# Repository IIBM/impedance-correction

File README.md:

# impedance-correction

This project involves the design, development and prototyping of an automated
**electrode impedance meter and corrector** for biological applications.

This will be achieved in the context of a basic embedded systems subject of the
Electronic Engineering career at the University of Buenos Aires:
[Laboratorio de Microcomputadoras](http://materias.fi.uba.ar/6609/).

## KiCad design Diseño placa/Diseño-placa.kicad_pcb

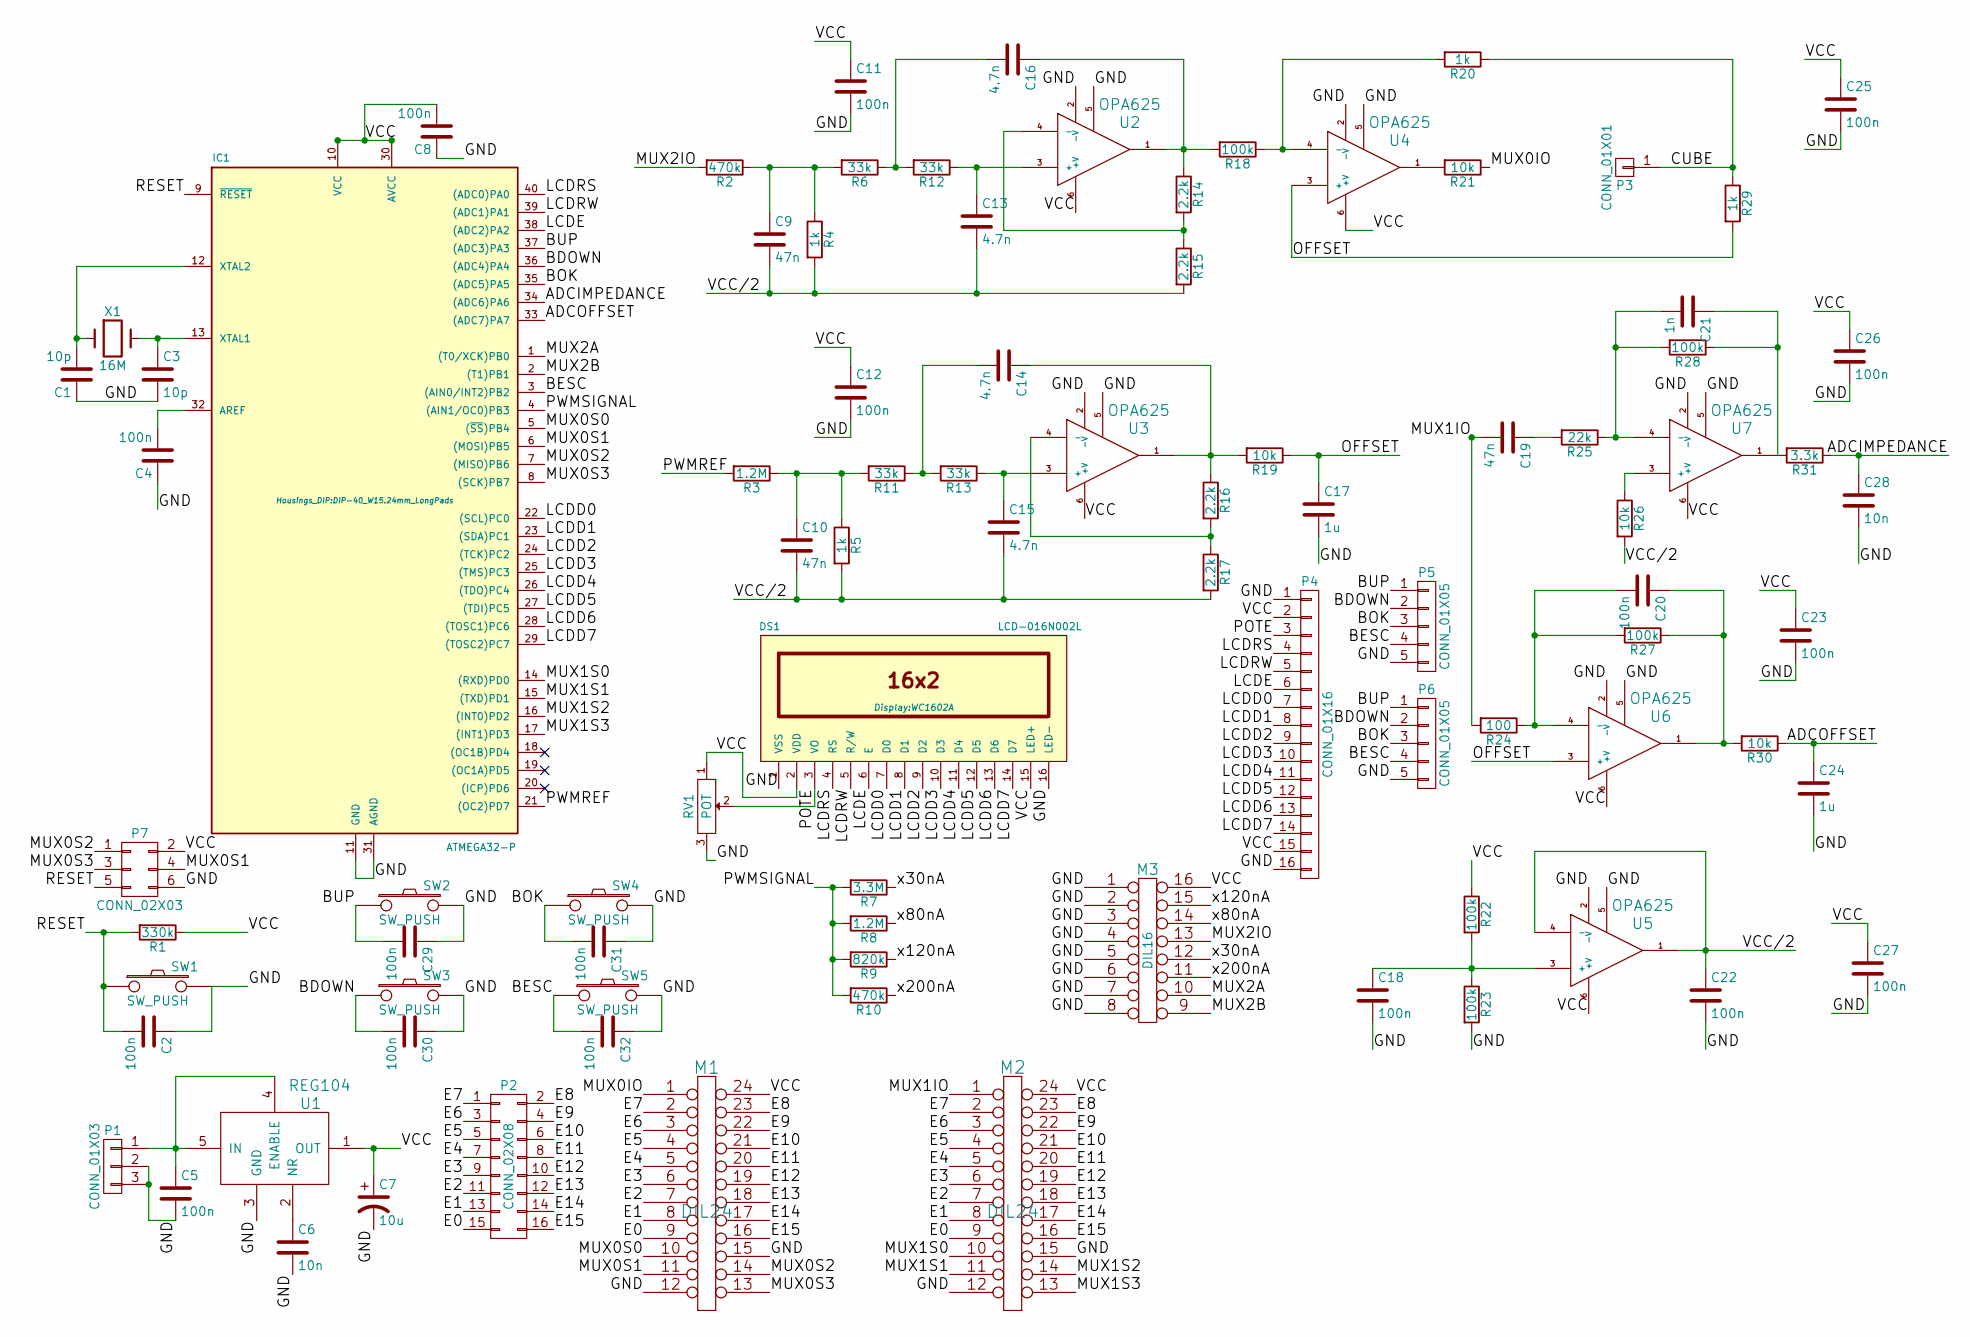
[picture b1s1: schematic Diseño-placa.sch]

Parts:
C1, C3: 10p; C_Rect_L4_W2.5_P2.5
C2, C4, C5, C8, C11, C12, C18, C20, C22, C23, C25, C26, C27, C29, C30, C31, C32: 100n; C_Rect_L4_W2.5_P2.5
C6: 10n; C_Rect_L4_W2.5_P2.5
C7: 10u; Elko_vert_11.2x6.3mm_RM2.5
C9, C10, C19: 47n; C_Rect_L4_W2.5_P2.5
C13, C14, C15, C16: 4.7n; C_Rect_L4_W2.5_P2.5
C17, C24: 1u; C_Rect_L7_W6_P5
C21: 1n; C_Rect_L4_W2.5_P2.5
C28: 10n; C_Rect_L7_W6_P5
DS1: LCD-016N002L; WC1602A
IC1: ATMEGA32-P; DIP-40_W15.24mm_LongPads
M1, M2: DIL24; SOIC-24_7.5x15.4mm_Pitch1.27mm
M3: DIL16; SOIC-16_3.9x9.9mm_Pitch1.27mm
P1: CONN_01X03; JACK_PWR
P2: CONN_02X08; Pin_Header_Angled_2x08
P3: CONN_01X01; Pin_Header_Straight_1x01
P4: CONN_01X16; Pin_Header_Straight_1x16
P5, P6: CONN_01X05; Pin_Header_Straight_1x05
P7: CONN_02X03; Pin_Header_Straight_2x03
R1: 330k; Resistor_Horizontal_RM10mm
R2, R10: 470k; Resistor_Horizontal_RM10mm
R3, R8: 1.2M; Resistor_Horizontal_RM10mm
R4, R5, R20, R29: 1k; Resistor_Horizontal_RM10mm
R6, R11, R12, R13: 33k; Resistor_Horizontal_RM10mm
R7: 3.3M; Resistor_Horizontal_RM10mm
R9: 820k; Resistor_Horizontal_RM10mm
R14, R15, R16, R17: 2.2k; Resistor_Horizontal_RM10mm
R18, R22, R23, R27, R28: 100k; Resistor_Horizontal_RM10mm
R19, R21, R26, R30: 10k; Resistor_Horizontal_RM10mm
R24: 100; Resistor_Horizontal_RM10mm
R25: 22k; Resistor_Horizontal_RM10mm
R31: 3.3k; Resistor_Horizontal_RM10mm
RV1: POT; Pin_Header_Straight_1x03
SW1, SW2, SW3, SW4, SW5: SW_PUSH; SW_PUSH-12mm
U1: REG104; TO-263-5Lead
U2, U3, U4, U5, U6, U7: OPA625; TSOT-6-MK06A_Handsoldering
X1: 16M; Crystal_HC49-U_Vertical

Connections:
/ADCIMPEDANCE: C28.1, IC1.34 ((ADC6)PA6), R31.1
/ADCOFFSET: C24.1, IC1.33 ((ADC7)PA7), R30.1
/BDOWN: C30.2, IC1.36 ((ADC4)PA4), P5.2, P6.2, SW3.1
/BESC: C32.2, IC1.3 ((AIN0/INT2)PB2), P5.4, P6.4, SW5.1
/BOK: C31.2, IC1.35 ((ADC5)PA5), P5.3, P6.3, SW4.1
/BUP: C29.2, IC1.37 ((ADC3)PA3), P5.1, P6.1, SW2.1
/CUBE: P3.1, R20.1, R29.1
/E0: M1.9, M2.9, P2.15
/E1: M1.8, M2.8, P2.13
/E2: M1.7, M2.7, P2.11
/E3: M1.6, M2.6, P2.9
/E4: M1.5, M2.5, P2.7
/E5: M1.4, M2.4, P2.5
/E6: M1.3, M2.3, P2.3
/E7: M1.2, M2.2, P2.1
/E8: M1.23, M2.23, P2.2
/E9: M1.22, M2.22, P2.4
/E10: M1.21, M2.21, P2.6
/E11: M1.20, M2.20, P2.8
/E12: M1.19, M2.19, P2.10
/E13: M1.18, M2.18, P2.12
/E14: M1.17, M2.17, P2.14
/E15: M1.16, M2.16, P2.16
/GND: C1.1, C2.1, C3.2, C4.1, C5.2, C6.2, C7.2, C8.1, C11.2, C12.2, C17.2, C18.2, C22.2, C23.2, C24.2, C25.2, C26.2, C27.2, C28.2, C29.1, C30.1, C31.1, C32.1, DS1.1 (VSS), DS1.16 (LED-), IC1.11 (GND), IC1.31 (AGND), M1.12, M1.15, M2.12, M2.15, M3.1, M3.2, M3.3, M3.4, M3.5, M3.6, M3.7, M3.8, P1.2, P1.3, P4.1, P4.16, P5.5, P6.5, P7.6, R23.2, RV1.3, SW1.2, SW2.2, SW3.2, SW4.2, SW5.2, U1.3 (GND), U2.2 (-V), U2.5, U3.2 (-V), U3.5, U4.2 (-V), U4.5, U5.2 (-V), U5.5, U6.2 (-V), U6.5, U7.2 (-V), U7.5
/LCDD0: DS1.7 (D0), IC1.22 ((SCL)PC0), P4.7
/LCDD1: DS1.8 (D1), IC1.23 ((SDA)PC1), P4.8
/LCDD2: DS1.9 (D2), IC1.24 ((TCK)PC2), P4.9
/LCDD3: DS1.10 (D3), IC1.25 ((TMS)PC3), P4.10
/LCDD4: DS1.11 (D4), IC1.26 ((TDO)PC4), P4.11
/LCDD5: DS1.12 (D5), IC1.27 ((TDI)PC5), P4.12
/LCDD6: DS1.13 (D6), IC1.28 ((TOSC1)PC6), P4.13
/LCDD7: DS1.14 (D7), IC1.29 ((TOSC2)PC7), P4.14
/LCDE: DS1.6 (E), IC1.38 ((ADC2)PA2), P4.6
/LCDRS: DS1.4 (RS), IC1.40 ((ADC0)PA0), P4.4
/LCDRW: DS1.5 (R/W), IC1.39 ((ADC1)PA1), P4.5
/MUX0IO: M1.1, R21.1
/MUX0S0: IC1.5 ((~SS~)PB4), M1.10
/MUX0S1: IC1.6 ((MOSI)PB5), M1.11, P7.4
/MUX0S2: IC1.7 ((MISO)PB6), M1.14, P7.1
/MUX0S3: IC1.8 ((SCK)PB7), M1.13, P7.3
/MUX1IO: C19.2, M2.1, R24.2
/MUX1S0: IC1.14 ((RXD)PD0), M2.10
/MUX1S1: IC1.15 ((TXD)PD1), M2.11
/MUX1S2: IC1.16 ((INT0)PD2), M2.14
/MUX1S3: IC1.17 ((INT1)PD3), M2.13
/MUX2A: IC1.1 ((T0/XCK)PB0), M3.10
/MUX2B: IC1.2 ((T1)PB1), M3.9
/MUX2IO: M3.13, R2.2
/OFFSET: C17.1, R19.1, R29.2, U4.3 (+), U6.3 (+)
/POTE: DS1.3 (VO), P4.3, RV1.2
/PWMREF: IC1.21 ((OC2)PD7), R3.2
/PWMSIGNAL: IC1.4 ((AIN1/OC0)PB3), R7.2, R8.2, R9.2, R10.2
/RESET: C2.2, IC1.9 (~RESET), P7.5, R1.2, SW1.1
/VCC: C7.1, C8.2, C11.1, C12.1, C23.1, C25.1, C26.1, C27.1, DS1.2 (VDD), DS1.15 (LED+), IC1.10 (VCC), IC1.30 (AVCC), M1.24, M2.24, M3.16, P4.2, P4.15, P7.2, R1.1, R22.1, RV1.1, U1.1 (OUT), U2.6 (+V), U3.6 (+V), U4.6 (+V), U5.6 (+V), U6.6 (+V), U7.6 (+V)
/VCC/2: C9.2, C10.2, C13.2, C15.2, C22.1, R4.2, R5.2, R15.2, R17.2, R26.2, U5.1, U5.4 (-)
/x30nA: M3.12, R7.1
/x80nA: M3.14, R8.1
/x120nA: M3.15, R9.1
/x200nA: M3.11, R10.1
unnamed: C1.2, IC1.12 (XTAL2), X1.1
unnamed: C3.1, IC1.13 (XTAL1), X1.2
unnamed: C4.2, IC1.32 (AREF)
unnamed: C5.1, P1.1, U1.4 (ENABLE), U1.5 (IN)
unnamed: C6.1, U1.2 (NR)
unnamed: C9.1, R2.1, R4.1, R6.2
unnamed: C10.1, R3.1, R5.1, R11.2
unnamed: C13.1, R12.1, U2.3 (+)
unnamed: C14.1, R16.1, R19.2, U3.1
unnamed: C14.2, R11.1, R13.2
unnamed: C15.1, R13.1, U3.3 (+)
unnamed: C16.1, R14.1, R18.2, U2.1
unnamed: C16.2, R6.1, R12.2
unnamed: C18.1, R22.2, R23.1, U5.3 (+)
unnamed: C19.1, R25.2
unnamed: C20.1, R27.1, R30.2, U6.1
unnamed: C20.2, R24.1, R27.2, U6.4 (-)
unnamed: C21.1, R28.1, R31.2, U7.1
unnamed: C21.2, R25.1, R28.2, U7.4 (-)
unnamed: R14.2, R15.1, U2.4 (-)
unnamed: R16.2, R17.1, U3.4 (-)
unnamed: R18.1, R20.2, U4.4 (-)
unnamed: R21.2, U4.1
unnamed: R26.1, U7.3 (+)

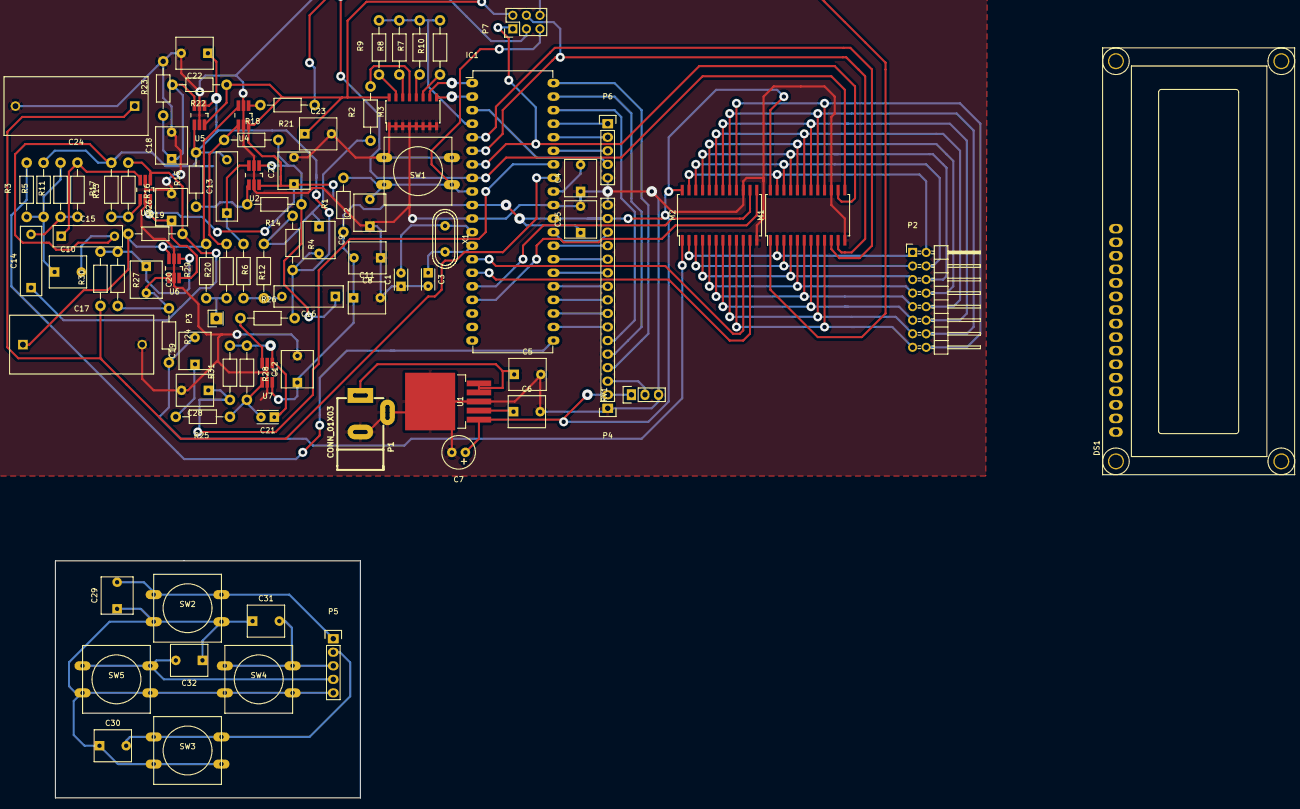
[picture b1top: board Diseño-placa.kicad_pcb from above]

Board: 2 copper layers, 57.1 x 44.4 mm, 89 parts (0 on the bottom side), 83 nets.

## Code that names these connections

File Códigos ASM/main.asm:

#ifdef AVRA
    .nolist
    .include "m32def.inc"
    .list
#endif


.include "configs.asm"
.include "pwm.asm"
.include "adc.asm"
.include "measure_routines.asm"
.include "MEDIR.asm"
.include "BCD.asm"
.include "LCD.asm"
.include "MENU.asm"
.include "CORREGIR_FIN.asm"


;||||||||||||||||||||||||||||||||||||||||||||||||||||||||||||||||||||||||||||||;
;|||||||||||||||||||||||||||||||||||| Main ||||||||||||||||||||||||||||||||||||;
;||||||||||||||||||||||||||||||||||||||||||||||||||||||||||||||||||||||||||||||;
MAIN:
    ldi     tmp,HIGH(RAMEND)
    out     SPH,tmp
    ldi     tmp,LOW(RAMEND)
    out     SPL,tmp  ; Stack pointer
    sei              ; Habilita las interrupciones (global)

;------------------------ Configuración de los puertos ------------------------;
;
;       PA0 --> RS  |                         PC0 --> D0  |
;       PA1 --> R/W | LCD                     PC1 --> D1  |
;       PA2 --> E   |                         PC2 --> D2  |
;       PA3 <-- ButtonLeft                    PC3 --> D3  | LCD
;       PA4 <-- ButtonRight                   PC4 --> D4  |
;       PA5 <-- ButtonOk                      PC5 --> D5  |
;       PA6 <== ADC: ImpedanceMeasure         PC6 --> D6  |
;       PA7 <== ADC: OffsetCalibration        PC7 --> D7  |
;
;
;       PB0 --> A   | MUX2                    PD0 --> S0  |
;       PB1 --> B   |                         PD1 --> S1  | MUX1
;       PB2 <== INT2: ButtonEsc               PD2 --> S2  |
;       PB3 ==> OC0: PWMSineWave              PD3 --> S3  |
;       PB4 --> S0  |                         PD4 *Unused*
;       PB5 --> S1  | MUX0                    PD5 *Unused*
;       PB6 --> S2  |                         PD6 *Unused*
;       PB7 --> S3  |                         PD7 ==> OC2: PWMOffsetAdjust
;
    ; Salidas y entradas
    ldi     tmp,0b00000111
    out     DDRA,tmp
    ldi     tmp,0b11111011
    out     DDRB,tmp
    ldi     tmp,0b11111111
    out     DDRC,tmp
    ldi     tmp,0b10001111
    out     DDRD,tmp

    ; Resistencias pull-up
    ldi     tmp,0b00111000
    out     PORTA,tmp
    ldi     tmp,0b00000100
    out     PORTB,tmp
    ldi     tmp,0b01110000
    out     PORTD,tmp

    ; Interrupción de escape
    ldi     tmp,(1<<INT2) ; Interrupción INT2 (flanco descendente por defecto)
    out     GICR,tmp

;------------------------------------------------------------------------------;
    jmp     MENU

    rjmp    MAIN ; Si se llega hasta aquí por error, se comienza de nuevo


;|//////////////////////////////////////|\\\\\\\\\\\\\\\\\\\\\\\\\\\\\\\\\\\\\|;
;|////////////////////////| Delay de 50 milisegundos |\\\\\\\\\\\\\\\\\\\\\\\\|;
;|//////////////////////////////////////|\\\\\\\\\\\\\\\\\\\\\\\\\\\\\\\\\\\\\|;
;
; Utiliza el Timer1. Solo usa el registro temporal, este nunca se salva.
;
DELAY_50ms:
    ldi     tmp,HIGH(TIMER1_50ms_DELAY_START)
    out     TCNT1H,tmp
    ldi     tmp,LOW(TIMER1_50ms_DELAY_START)
    out     TCNT1L,tmp                        ; Carga del contador del Timer1

    ldi     tmp,TIMER1_CLOCK_64_PRESCALER
    out     TCCR1B,tmp                        ; Activación del Timer1

keep_waiting:
    in      tmp,TIFR
    sbrs    tmp,TOV1      ; Saltea si el flag de overflow está encendido
    rjmp    keep_waiting

    ldi     tmp,TIMER1_OFF
    out     TCCR1B,tmp                        ; Desactivación del Timer1
    ldi     tmp,(1<<TOV1)
    out     TIFR,tmp                          ; Borrado del flag de overflow

    ret


;|//////////////////////////////////////|\\\\\\\\\\\\\\\\\\\\\\\\\\\\\\\\\\\\\|;
;|///////////////////////| Delay en segundos (1 a 255) |\\\\\\\\\\\\\\\\\\\\\\|;
;|//////////////////////////////////////|\\\\\\\\\\\\\\\\\\\\\\\\\\\\\\\\\\\\\|;
;
; param (R17) <- cantidad de segundos, 1 < param < 255
; Utiliza la rutina de delay de 50 ms. Salva todos los registros que arruina.
;
DELAY_PARAM_SECONDS:
    push    iter
    push    iter2 ; Registros salvados en el stack

    mov     iter,param ; Contador de segundos, se carga con el parámetro
loop_1s:
    ldi     iter2,20   ; Contador de 50 milisegundos: 20 * 50 ms = 1000 ms = 1 s
loop_50ms:
    rcall   DELAY_50ms
    dec     iter2      ; Decremento del contador de 50 milisegundos
    brne    loop_50ms  ; Si se contaron 20 vueltas de 50 ms se deja de repetir
    dec     iter       ; Decremento del contador de segundos
    brne    loop_1s    ; Si se contaron 60 vueltas de 1 s se deja de repetir

    pop     iter2
    pop     iter  ; Registros recuperados del stack
    ret

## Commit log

2015-09-19 Inicialización del repositorio
    * .gitignore y README.mk
    * Plantilla del anteproyecto creada
2015-09-21 Completar ciertas secciones
2015-09-21 Comentar paquete unidades SI
    No lo necesitamos aún y en mi computadora no funciona así como está.
    Además, cambié el tamaño de la sangría.
2015-09-21 Informe actualizado
2015-09-22 Revisión general y agregado de diagramas
    * Lógica general, orden de la información en las secciones.
    * Diagrama de flujo, hecho con 'dia'.
    * Diagrama en bloques, hecho con 'dia'.
2015-09-22 Correcciones menores
    Después las paso al informe en serio, cuando me funcione Latex.
2015-09-22 Correcciones menores
2015-09-29 Actualización de correcciones y tabla de componentes
2015-09-30 Gantt y detalles finales
    (Faltan los precios de los componentes)
2015-10-01 Agregado de precios y modificaciones menores
    * Precios obtenidos de mercadolibre y/o con un dolar estimativo de $12
    * Cambio de nombre del directorio anteproyecto/img/dia hacia anteproyecto/img/src
    * Leves modificaciones del Gantt y paso del mismo al formato ODF, exportando en PDF para evitar el uso de imágenes
    * Cambios menores en la carátula para ajustar el docente guía, el curso y detalles de formato
2015-10-01 Error de tipeo en el diagrama en bloques corregido
2015-10-21 Comienzo del esquemático
2015-10-21 Codigos de Assembler
2015-10-30 Actualización del esquemático para simulación
    Nota: se eliminan y dejan de versionar los archivos .raw
    de LTspice, ya que son muy grandes y se pueden regenerar
    simulando nuevamente. Así se evitan problemas al hacer
    'push' hacia el repositorio remoto.
2015-11-02 Comienzo esquemático Kicad
2015-11-03 Renombrado: anteproyecto -> Anteproyecto
2015-11-03 Actualización del esquemático (!)
    (!): la simulación no está funcionando en este momento.
2015-11-03 Cambios en el esquemático (*) (!)
    (*) Se solucionó el problema de que no simulaba.
    (!) El método propuesto para el offset no funciona.
2015-11-06 Espacio sobrante y falta de tilde en "Códigos ASM"
2015-11-07 Rutina de medir, corregir y calibrar (LCD)
2015-11-07 Cambio de interrupciones por polling
2015-11-09 Avances esquemático en Kicad
2015-11-13 Agregado de algunas rutinas y archivos de ayuda
2015-11-14 Más del esquemático Kicad
2015-11-15 Esquemático de LTspice actualizado
    * Actualización con la última versión enviada por Ariel.
    * Eliminación del .plt que puede ya no ser válido para el nuevo .asc.
2015-11-16 Más esquemático Kicad
2015-11-17 Correcciones esquemático y asociación de componentes Kicad
2015-11-19 Medir y Corregir
2015-11-20 Reorganización del código y nuevas rutinas
    * Se agregó un archivo de Excel (OpenOffice) con cálculos de calibración.
    * Se renombró el directorio Extras Octave, a Extras, para poner contenido
    variado, incluyendo la planilla de cálculos mencionada.
    * Se reacomodó el código pensando en la futura integración de todo.
    * Se renombraron archivos y movieron contenidos, separando las partes.
    * Se crearon nuevas rutinas en el manejo del PWM y el multiplexor MUX2.
2015-11-22 Rutina resultados
2015-11-22 Comienzo PCB
2015-11-22 Esquema informe
2015-11-24 Informe: Listado de componentes y esquemático
2015-11-24 Actualización del informe
    * Se actualizó el diagrama en bloques.
    * Se exportó el esquemático en PDF porque estaba pixelado.
    * ADC.asm renombrado a adc.asm
2015-11-24 Actualización PCB
    *Conector de programación
    *Capacitores de los pulsadores
2015-11-24 Actualizaciones de código
    * Varios reordenamientos y cambios menores.
    * Rutina de muestreo del ADC.
2015-11-25 PCB terminado
2015-11-25 Corrección tamaño de capacitores
2015-11-28 Actualización del informe
    * Revisión de los textos del anteproyecto.
    * Agregado de la planilla de cálculos de calibración.
    * Archivo assembly renombrado.
2015-11-28 Mejoramiento y agregado de rutinas
    * Mejoras generales, revisión del código.
    * Rutinas de delay de 50 ms y delay en segundos (de 1 a 255).
    * Rutina de medición de pico desde la tabla en RAM del ADC.
2015-11-29 Reacomodamiento general y resolución de problemas
    * Rutina que obtiene la medición escalando por el valor calibrado de cada
    rango.
    * "Medir y Corregir.asm" renombrado a "MENU.asm"
    * Detalles menores y agregado de tablas en flash con valores asociados a los
    rangos.
    * .gitignore actualizado para ignorar los archivos *.net de LTspice.
2015-11-29 Cambios varios
2015-11-29 Modificaciones menores en el código + informe.pdf
    * Agregado de rutina inicial de activación del PWM de Offset.
    * informe.pdf eliminado por error agregado.
2015-11-29 Cambios código
2015-11-29 Agregado de interrupción para el botón de escape
2015-11-30 Actualización
2015-11-30 PCB corrección de pistas conflictivas
2015-11-30 Otra más
2015-11-30 JOJOO
2015-12-01 Última versión PCB
2015-12-01 Modificaciones varias
    * Makefile.
    * Actualización del .gitignore.
    * Cambios menores de integración en el código.
2015-12-01 Cambio delay
2015-12-01 Actualización informe
2015-12-01 Menú actualizado
2015-12-01 Más informe
2015-12-01 Archivos PDF recortados
2015-12-01 Cambios varios y de último momento (warning!)
2015-12-01 Informe final
2015-12-01 Agregado del código entregado en PDF
2015-12-04 Actualización para entrega de compromiso
    Los rangos de medición fueron reducidos por problemas de hardware, el código fue
    adaptado de forma tal que funcione para estos nuevos valores. También se
    agregaron algunas funcionalidades, incluyendo la finalización de la rutina de
    corrección.
2015-12-04 Actualización de recursos del informe
    * Diagrama de flujo.
    * PCB del circuito.
2015-12-04 Agregado de gráfico del osciloscopio
2015-12-04 Osciloscopio en negro
2015-12-04 Agregado de la última versión del código
2015-12-10 Retoque y refinado del informe
    * Limpieza de archivos temporarios.
    * Explicación de la sección de cálculos.
    * Uso de listings para incluir el código fuente.
